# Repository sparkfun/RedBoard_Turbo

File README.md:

SparkFun RedBoard Turbo
========================================

[*SparkFun RedBoard Turbo (DEV-14812)*](https://www.sparkfun.com/products/14812)

The RedBoard Turbo is an Arduino-sized breakout for the Atmel [ATSAMD21G18](http://www.atmel.com/devices/ATSAMD21G18A.aspx), a 32-bit ARM Cortex-M0+ processor with 4MB external flash, 32KB SRAM, and an operating speed of up to 48MHz. The SAMD21 is compatible with the Arduino IDE, and libraries for the Arduino Zero. With the UF2 bootloader, programming is easier than ever!

Repository Contents
-------------------

* **/Documentation** - Data sheets, additional product information
* **/Firmware** - UF2 Bootloader
* **/Hardware** - Eagle design files (.brd, .sch)
* **/Production** - Production panel files (.brd)

Documentation
--------------
* **[SparkFun Arduino Boards](https://github.com/sparkfun/Arduino_Boards)** - Arduino Boards.
* **[Hookup Guide](https://learn.sparkfun.com/tutorials/redboard-turbo-hookup-guide)** - Basic hookup guide for the RedBoard Turbo.
* **[SparkFun Fritzing Repo](https://github.com/sparkfun/Fritzing_Parts/blob/master/products/14812_sfe_redboard_turbo.fzpz)** - Fritzing diagrams for SparkFun products.
* **[SparkFun Graphical Datasheets](https://github.com/sparkfun/Graphical_Datasheets)** - Graphical Datasheets for various SparkFun products.

License Information
-------------------

This product is _**open source**_! 

Please review the LICENSE.md file for license information. 

If you have any questions or concerns on licensing, please contact technical support on our [SparkFun forums](https://forum.sparkfun.com/viewforum.php?f=152).

Distributed as-is; no warranty is given.

- Your friends at SparkFun.

_<COLLABORATION CREDIT>_

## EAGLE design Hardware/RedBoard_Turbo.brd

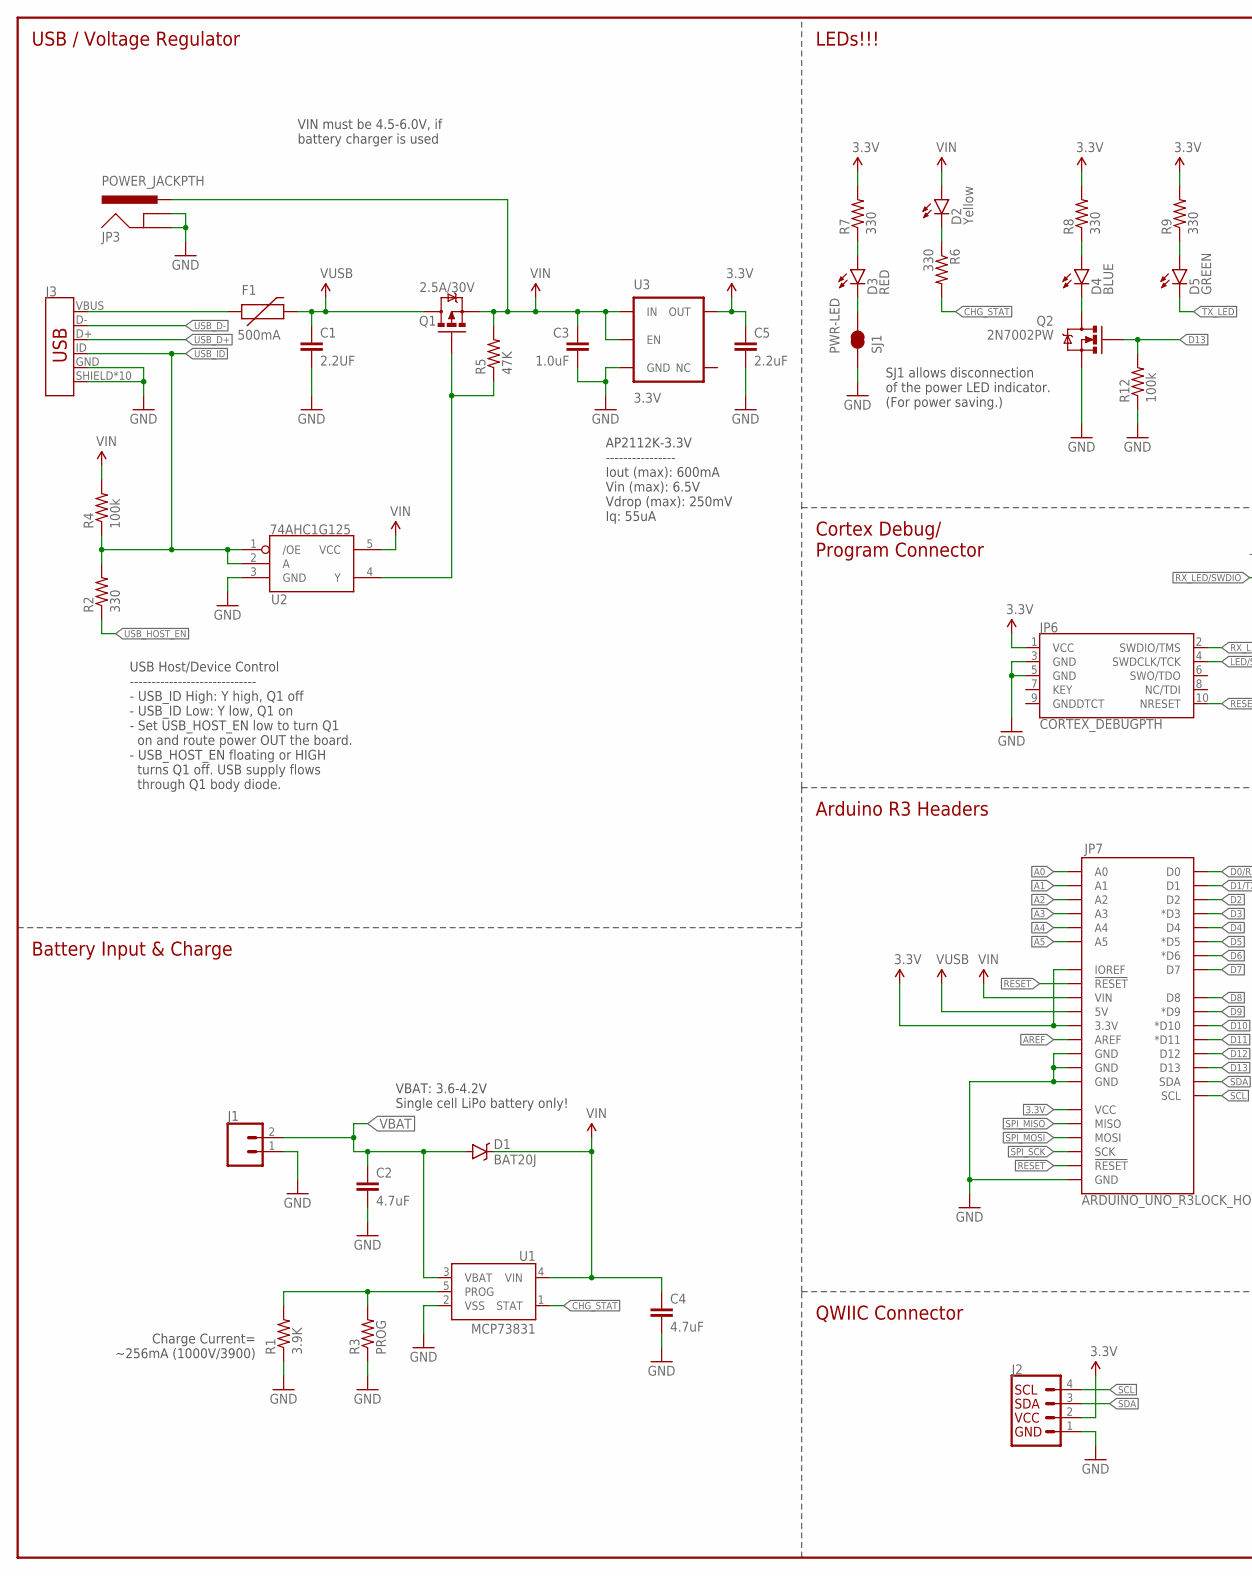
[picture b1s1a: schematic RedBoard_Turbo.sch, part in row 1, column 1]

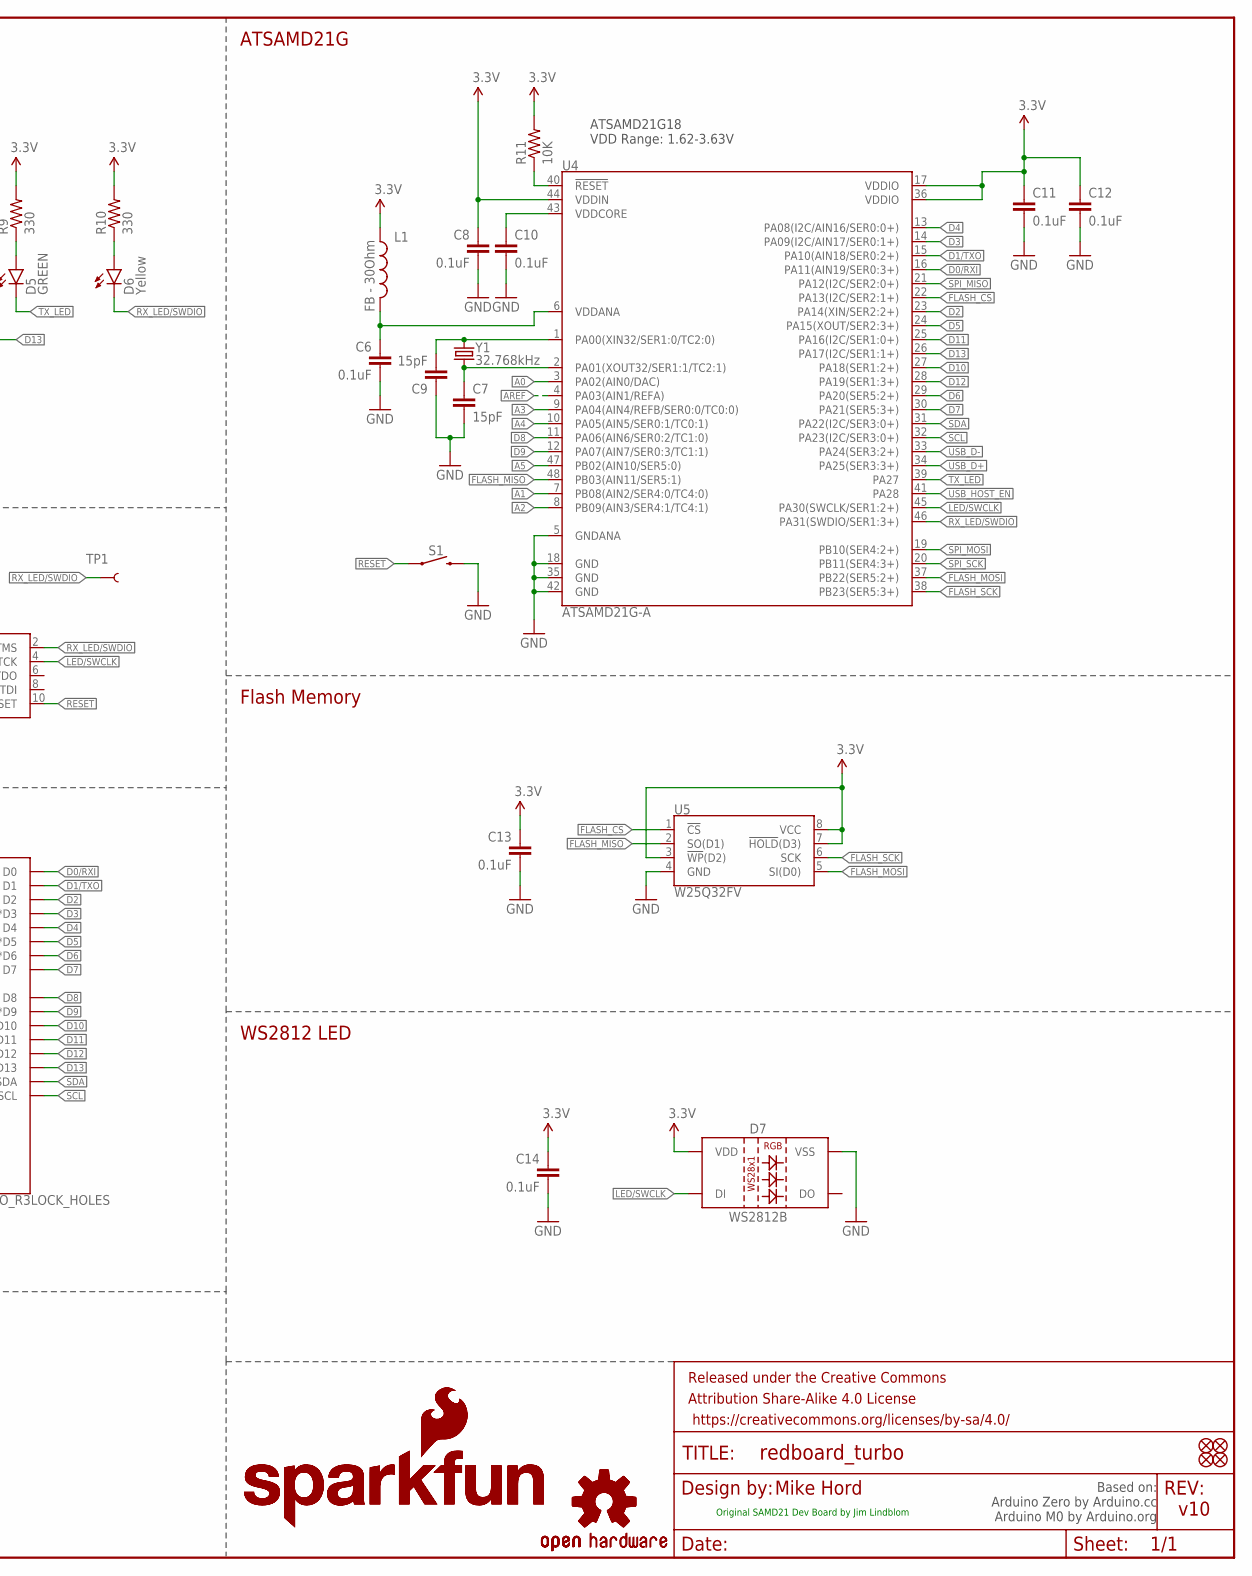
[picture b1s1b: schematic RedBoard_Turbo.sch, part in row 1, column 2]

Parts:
C1: 2.2UF; 1206@1
C2, C4: 4.7uF; 0603-CAP
C3: 1.0uF; 0805
C5: 2.2uF; 0603-CAP
C6, C8, C10, C11, C12, C13, C14: 0.1uF; 0603-CAP
C7, C9: 15pF; 0603-CAP
D1: BAT20J; SOD-323
D2, D6: Yellow; LED-0603
D3: RED; LED-0603
D4: BLUE; LED-0603
D5: GREEN; LED-0603
D7: WS2812B
F1: 500mA; PTC-1206
FID1, FID2, FID3, FID4: FIDUCIAL1X2; FIDUCIAL-1X2
FRAME1: FRAME-LEDGER; CREATIVE_COMMONS
J1: CONN_02JST-PTH-2; JST-2-PTH
J2: QWIIC_CONNECTORJS-1MM; 1X04_1MM_RA
J3: USB_MICRO-B_HALF_PTH_MILL; USB-MICROB-PTH-MILL
JP3: POWER_JACKPTH; POWER_JACK_PTH
JP6: CORTEX_DEBUGPTH; 2X5-PTH-1.27MM
JP7: ARDUINO_UNO_R3LOCK_HOLES; ARDUINO_R3_LOCK_HOLES
L1: FB - 30Ohm; 0603
LOGO1: SFE_LOGO_NAME_FLAME.2_INCH; SFE_LOGO_NAME_FLAME_.2
LOGO2: SFE_LOGO_NAME_FLAME.3_INCH; SFE_LOGO_NAME_FLAME_.3
LOGO3: OSHW-LOGOS; OSHW-LOGO-S
LOGO4: OSHW-LOGOL; OSHW-LOGO-L
Q1: 2.5A/30V; SOT23-3
Q2: 2N7002PW; SOT323
R1: 3.9K; 0603
R2, R6, R7, R8, R9, R10: 330; 0603-RES
R3: PROG; 1/6W-RES
R4, R12: 100k; 0603-RES
R5: 47K; 0603-RES
R11: 10K; 0603-RES
S1: MOMENTARY-SWITCH-SPST-SMD-5.2-TALL-REDUNDANT; TACTILE_SWITCH_SMD_5.2MM
SJ1: PWR-LED; PAD-JUMPER-2-NC_BY_TRACE_NO_SILK
TP1: TEST-POINTTP_15TH_THRU; TP_15TH
U1: MCP73831; SOT23-5
U2: 74AHC1G125; SOT23-5
U3: 3.3V; SOT23-5
U4: ATSAMD21G-A; TQFP-48
U5: W25Q32FV; SOIC-8
Y1: 32.768kHz; CRYSTAL-SMD-3.2X1.5MM

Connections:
3.3V: C5.1, C8.1, C11.1, C12.1, C13.1, C14.1, D7.1 (VDD), J2.2, JP6.1 (VCC), JP7.3.3V, JP7.IOREF, JP7.VCC, L1.1, R7.2, R8.2, R9.2, R10.2, R11.2, U3.5 (OUT), U4.17 (VDDIO), U4.36 (VDDIO), U4.44 (VDDIN), U5.3 (!WP!(D2)), U5.7 (!HOLD!(D3)), U5.8 (VCC)
!RESET: JP6.10 (NRESET), JP7.RESET@1 (!RESET!), JP7.RESET@2 (!RESET!), R11.1, S1.1, S1.2 (1), U4.40 (!RESET!)
A0: JP7.A0, U4.3 (PA02(AIN0/DAC))
A1: JP7.A1, U4.7 (PB08(AIN2/SER4:0/TC4:0))
A2: JP7.A2, U4.8 (PB09(AIN3/SER4:1/TC4:1))
A3: JP7.A3, U4.9 (PA04(AIN4/REFB/SER0:0/TC0:0))
A4: JP7.A4, U4.10 (PA05(AIN5/SER0:1/TC0:1))
A5: JP7.A5, U4.47 (PB02(AIN10/SER5:0))
AREF: JP7.AREF, U4.4 (PA03(AIN1/REFA))
CHG_STAT: R6.2, U1.1 (STAT)
D0/RXI: JP7.D0, U4.16 (PA11(AIN19/SER0:3+))
D1/TXO: JP7.D1, U4.15 (PA10(AIN18/SER0:2+))
D2: JP7.D2, U4.23 (PA14(XIN/SER2:2+))
D3: JP7.D3 (*D3), U4.14 (PA09(I2C/AIN17/SER0:1+))
D4: JP7.D4, U4.13 (PA08(I2C/AIN16/SER0:0+))
D5: JP7.D5 (*D5), U4.24 (PA15(XOUT/SER2:3+))
D6: JP7.D6 (*D6), U4.29 (PA20(SER5:2+))
D7: JP7.D7, U4.30 (PA21(SER5:3+))
D8: JP7.D8, U4.11 (PA06(AIN6/SER0:2/TC1:0))
D9: JP7.D9 (*D9), U4.12 (PA07(AIN7/SER0:3/TC1:1))
D10: JP7.D10 (*D10), U4.27 (PA18(SER1:2+))
D11: JP7.D11 (*D11), U4.25 (PA16(I2C/SER1:0+))
D12: JP7.D12, U4.28 (PA19(SER1:3+))
D13: JP7.D13, Q2.1 (G), R12.2, U4.26 (PA17(I2C/SER1:1+))
FLASH_CS: U4.22 (PA13(I2C/SER2:1+)), U5.1 (!CS!)
FLASH_MISO: U4.48 (PB03(AIN11/SER5:1)), U5.2 (SO(D1))
FLASH_MOSI: U4.37 (PB22(SER5:2+)), U5.5 (SI(D0))
FLASH_SCK: U4.38 (PB23(SER5:3+)), U5.6 (SCK)
GND: C1.2, C2.2, C3.2, C4.2, C5.2, C6.2, C7.2, C8.2, C9.1, C10.2, C11.2, C12.2, C13.2, C14.2, D7.3 (VSS), J1.1, J2.1, J3.GND, J3.SHIELD, J3.SHIELD2 (SHIELD), J3.SHIELD3 (SHIELD), J3.SHIELD4 (SHIELD), J3.SHIELD5 (SHIELD), J3.SHIELD6 (SHIELD), J3.SHIELD7 (SHIELD), J3.SHIELD8 (SHIELD), J3.SHIELD9 (SHIELD), J3.SHIELD10 (SHIELD), JP3.GND, JP3.GNDBREAK, JP6.3 (GND), JP6.5 (GND), JP7.GND@1 (GND), JP7.GND@2 (GND), JP7.GND@3 (GND), JP7.GND@4 (GND), Q2.2 (S), R1.1, R3.1, R12.1, S1.3 (2), S1.4 (2), SJ1.1, U1.2 (VSS), U2.3 (GND), U3.2 (GND), U4.5 (GNDANA), U4.18 (GND), U4.35 (GND), U4.42 (GND), U5.4 (GND)
LED/SWCLK: D7.4 (DI), JP6.4 (SWDCLK/TCK), U4.45 (PA30(SWCLK/SER1:2+))
unnamed: F1.1, J3.VBUS
unnamed: C9.2, U4.1 (PA00(XIN32/SER1:0/TC2:0)), Y1.P$2 (2)
unnamed: D4.C, Q2.3 (D)
unnamed: C7.1, U4.2 (PA01(XOUT32/SER1:1/TC2:1)), Y1.P$1 (1)
unnamed: D3.A, R7.1
unnamed: D4.A, R8.1
unnamed: D2.C, R6.1
unnamed: D5.A, R9.1
unnamed: D6.A, R10.1
unnamed: D3.C, SJ1.2
unnamed: R1.2, R3.2, U1.5 (PROG)
RX_LED/SWDIO: D6.C, JP6.2 (SWDIO/TMS), TP1.P$1, U4.46 (PA31(SWDIO/SER1:3+))
SCL: J2.4, JP7.SCL, U4.32 (PA23(I2C/SER3:0+))
SDA: J2.3, JP7.SDA, U4.31 (PA22(I2C/SER3:0+))
SPI_MISO: JP7.MISO, U4.21 (PA12(I2C/SER2:0+))
SPI_MOSI: JP7.MOSI, U4.19 (PB10(SER4:2+))
SPI_SCK: JP7.SCK, U4.20 (PB11(SER4:3+))
TX_LED: D5.C, U4.39 (PA27)
USB_D+: J3.D+, U4.34 (PA25(SER3:3+))
USB_D-: J3.D-, U4.33 (PA24(SER3:2+))
USB_HOST_EN: R2.1, U4.41 (PA28)
USB_HOST_POWER_EN: Q1.1 (G), R5.1, U2.4 (Y)
USB_ID: J3.ID, R2.2, R4.1, U2.1 (/OE), U2.2 (A)
VBAT: C2.1, D1.A, J1.2, U1.3 (VBAT)
VDDANA: C6.1, L1.2, U4.6 (VDDANA)
VDDCORE: C10.1, U4.43 (VDDCORE)
VIN: C3.1, C4.1, D1.C, D2.A, JP3.PWR, JP7.VIN, Q1.2 (S), R4.2, R5.2, U1.4 (VIN), U2.5 (VCC), U3.1 (IN), U3.3 (EN)
VUSB: C1.1, F1.2, JP7.5V, Q1.3 (D)

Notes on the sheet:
USB / Voltage Regulator
LEDs!!!
Cortex Debug/ Program Connector
Arduino R3 Headers
ATSAMD21G
Mike Hord
v10
Charge Current= ~256mA (1000V/3900)
Battery Input & Charge
SJ1 allows disconnection of the power LED indicator. (For power saving.)
VIN must be 4.5-6.0V, if battery charger is used
ATSAMD21G18 VDD Range: 1.62-3.63V
Based on: Arduino Zero by Arduino.cc Arduino M0 by Arduino.org
AP2112K-3.3V ---------------- Iout (max): 600mA Vin (max): 6.5V Vdrop (max): 250mV Iq: 55uA
USB Host/Device Control ----------------------------- - USB_ID High: Y high, Q1 off - USB_ID Low: Y low, Q1 on - Set USB_HOST_EN low to turn Q1 on and route power OUT the board. - USB_HOST_EN floating or HIGH turns Q1 off. USB supply flows through Q1 body diode.
VBAT: 3.6-4.2V Single cell LiPo battery only\!
QWIIC Connector
WS2812 LED
Flash Memory
Original SAMD21 Dev Board by Jim Lindblom

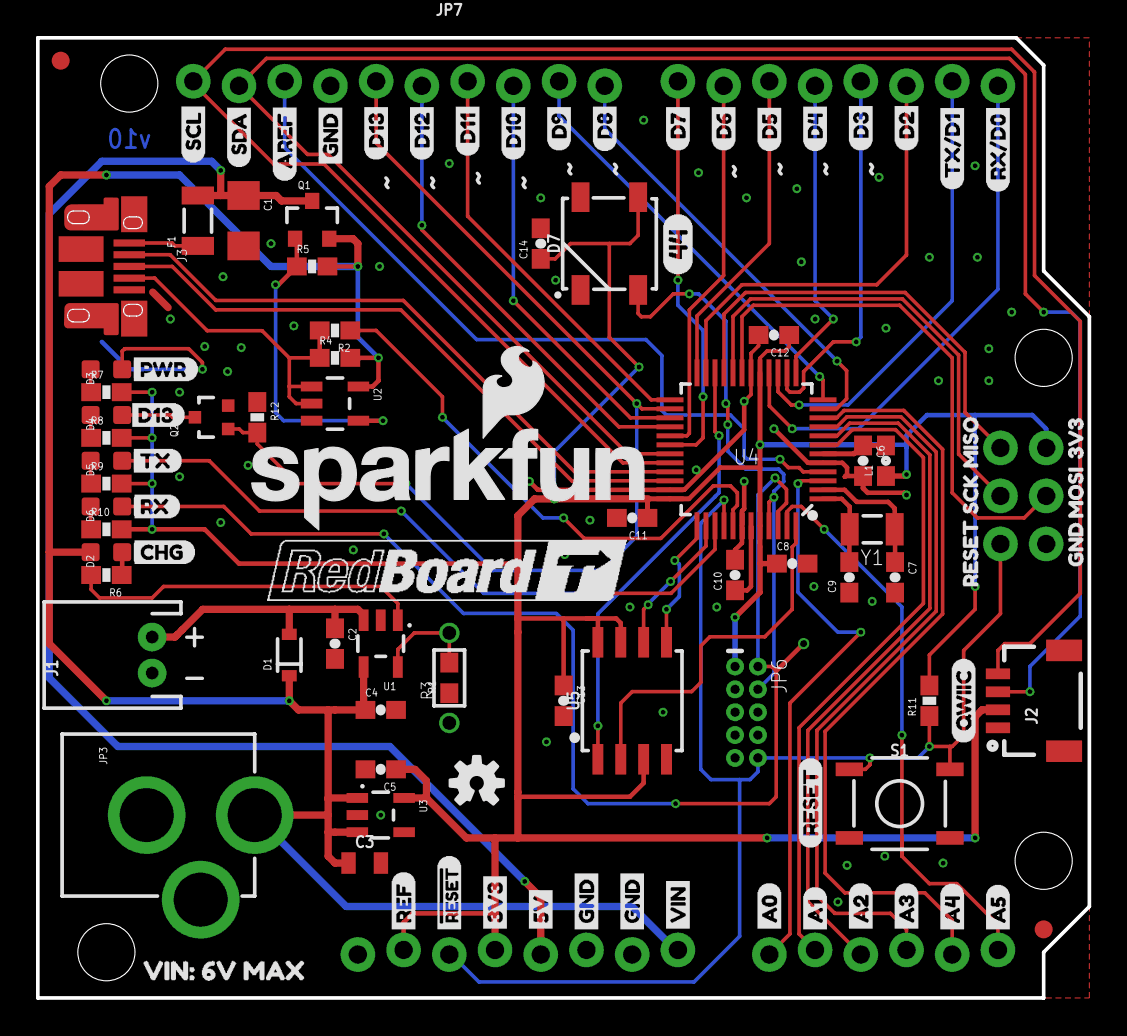
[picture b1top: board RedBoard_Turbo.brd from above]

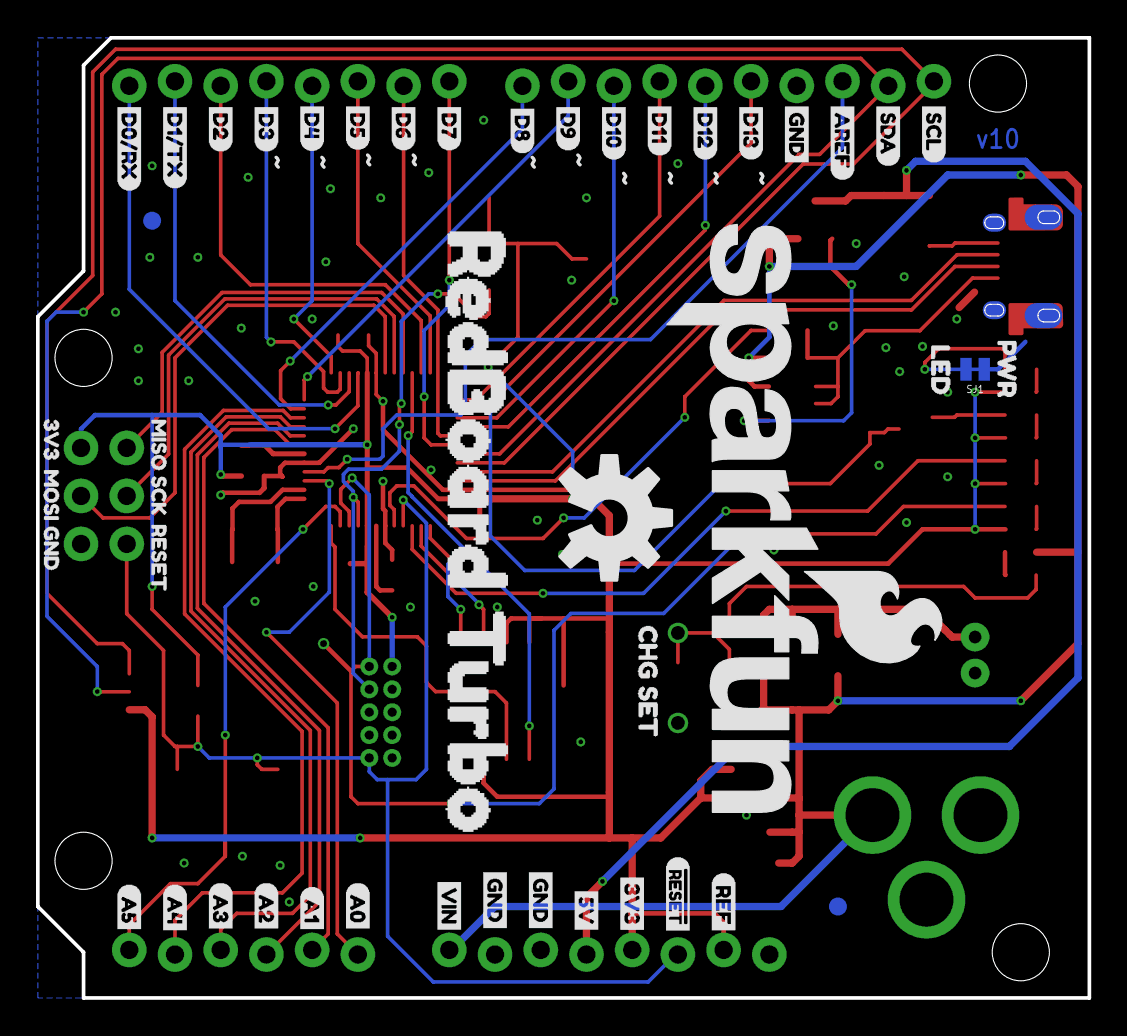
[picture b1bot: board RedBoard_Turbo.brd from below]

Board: 2 copper layers, 58.4 x 53.3 mm, 149 parts (46 on the bottom side), 58 nets.

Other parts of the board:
U$1, U$44: #RESET1
U$2: 3V317
U$3: 5V18
U$4: CHG30
U$5: RX#D015
U$6: TX#D114
U$7: D213
U$8: D312
U$9: D411
U$10: D510
U$11: D69
U$12: D78
U$13: D87
U$14: D96
U$15: D105
U$16: D114
U$17: D123
U$18: D132
U$19, U$36, U$37: GND16
U$20, U$81: SDA1
U$21, U$80: SCL0
U$22: TX28
U$23: RX29
U$24: PWR26
U$25: D1327
U$26: REF0
U$27, U$53: AREF2
U$28: QWIIC31
U$29: A020
U$30: A121
U$31: A222
U$32: A323
U$33: A424
U$34: A525
U$35: VIN19
U$38: GND7
U$39: MOSI4
U$40: 3V36
U$41: SCK5
U$42: MISO3
U$43, U$83: RESET0
U$45: 3V325
U$46: 3V30
U$47: A018
U$48: A119
U$49: A220
U$50: A321
U$51: A422
U$52: A523
U$54: LED1
U$55: D0#RX17
U$56: D1#TX15
U$57: 5V26
U$58: D79
U$59: D88
U$60: D97
U$61: D106
U$62: D115
U$63: D124
U$64: D133
U$65: D214
U$66: D313
U$67: D412
U$68: D511
U$69: D610
U$70, U$71, U$72: GND24
U$73: GND33
U$74: PWR0
U$75: MISO30
U$76: MOSI34
U$77: REF28
U$78: RESET32
U$79: SCK31
U$82: VIN27
U$84: 440
U$85: REDBOARD_TURBO1
U$86: BITMAP#JPG
U$87: CHG_SET1
U$88: VIN#_6V_MAX2

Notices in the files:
parts and their libraries:
SparkFun-Capacitors: Licensing: Creative Commons ShareAlike 4.0 International - https://creativecommons.org/licenses/by-sa/4.0
SparkFun-Aesthetics: Released under the Creative Commons Attribution Share-Alike 4.0 License
SparkFun-Aesthetics: https://creativecommons.org/licenses/by-sa/4.0
